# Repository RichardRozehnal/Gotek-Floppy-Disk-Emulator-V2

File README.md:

# Gotek Floppy Disk Emulator V2

Emulátor disketové mechaniky starých počítačů a různých zařízení. Software se do počítače nahrává z obrazu originálního disku (např. ADF pro Amigu), který je uložen na USB flash disku. Tato verze hardwaru využívá firmware [FlashFloppy](https://github.com/keirf/FlashFloppy/wiki), který přidává spoustu nových funkcí a vylepšení oproti standardnímu Goteku. Na uvedém odkazu tvůrce, najdete detailní popisy všech funkcí a nastavení a také nejnovější firmware.

## Seznam součástek

| **Ref**                                                                                                  | **Qnty** | **Value**                   | **Cmp name**                   |
| -------------------------------------------------------------------------------------------------------- | :------: | --------------------------- | ------------------------------ |
| BZ1,                                                                                                     | 1        | 5V Active Buzzer 12mm       | Buzzer                         |
| C1, C2, C4, C7, C8, C9, C10, C12,                                                                        | 8        | 100nF                       | C                              |
| C3, C11,                                                                                                 | 2        | 10uF                        | C                              |
| C5, C6,                                                                                                  | 2        | 22pF                        | C                              |
| C13,                                                                                                     | 1        | 4.7uF/16V                   | CP                             |
| D1,                                                                                                      | 1        | LED Green                   | LED                            |
| D2,                                                                                                      | 1        | 1N4148                      | D                              |
| J1,                                                                                                      | 1        | Power Connector             | Conn\_01x04                    |
| J2,                                                                                                      | 1        | OLED Display 0.91" Module   | OLED\_Display\_0.91"\_Module   |
| J3,                                                                                                      | 1        | USB\_A                      | USB\_A                         |
| J5,                                                                                                      | 1        | Programming Connector       | Conn\_02x05\_Odd\_Even         |
| J6,                                                                                                      | 1        | Floppy Data Connector       | Conn\_02x17\_Odd\_Even         |
| Q1,                                                                                                      | 1        | MMBT2222                    | Q\_NPN\_BEC                    |
| Q2, Q3, Q4, Q5, Q6, Q7,                                                                                  | 6        | BSS123                      | BSS123                         |
| R1,                                                                                                      | 1        | 4K7                         | R                              |
| R2, R3, R7, R8, R9, R10, R11, R12, R13, R14, R15, R16, R17, R18, R19, R20, R21, R22, R23, R24, R25, R26, | 22       | 1K                          | R                              |
| R4, R27                                                                                                  | 2        | 10K                         | R                              |
| R5, R6,                                                                                                  | 2        | 22R                         | R                              |
| SW1,                                                                                                     | 1        | KY040 Rotary Encoder Module | KY040\_Rotary\_Encoder\_Module |
| SW2,                                                                                                     | 1        | DIP Switch                  | DIP\_Switch                    |
| U1,                                                                                                      | 1        | AMS1117-3.3                 | AMS1117-3.3                    |
| U2,                                                                                                      | 1        | STM32F105RBTx               | STM32F105RBTx                  |
| U3,                                                                                                      | 1        | STMPS2141                   | STMPS2141                      |
| U4,                                                                                                      | 1        | 74HCT04                     | 74HCT04                        |
| Y1,                                                                                                      | 1        | 8MHz                        | Crystal                        |

## Oživení

### Programování mikrokontroléru pomocí ST-Link V2

1. stáhněte si a nainstalujte flashovací program STM32-ST-Link Utility na webu [st.com](https://www.st.com/en/development-tools/stsw-link004.html).
2. propojte ST-Link V2 a Gotek V2 vývody SWCLK, SWDIO, GND a +3.3V
3. připojte ST-Link V2 k PC a spusťte flashovací program
4. připojte se na MCU přes menu Target/Connect
5. přes menu File/Open File vyberte soubor FF_Gotek-v3.20.hex (nebo jiný, který chcete nahrát do MCU)
6. spusťte flashování přes menu Target/Program & Verify a Start

### Nastavení DIP přepínače SW2

Pro Amigu, Atari ST a další počítače je nastavení:

| **sig** | **zap/vyp** | **funkce**                              |
| :-----: | :---------: | --------------------------------------- |
| DC1     | OFF         |                                         |
| DC2     | ON          |                                         |
| J5      | OFF         |                                         |
| JC      | OFF         |                                         |
| JB      | ON          | zapnutí/vypnutí emulace zvuku mechaniky |
| S0      | ON          |                                         |
| S1      | OFF         |                                         |

### Příprava USB flash disku a základní operace

1. USB flash disk naformátujte na FAT32 a nahrajte na něj obrazy disků, které budete chtít spouštět, např. ADF pro Amigu
2. připojte Gotek V2 s vloženým USB flash diskem k Amize (místo interního floppy disku), napájecí konektor je dobré před zapojením změřit, abyste do Goteku V2 nepustili 12V místo 5V, kvůli obrácení konektoru!
3. zapněte Amigu, na displeji se zobrazí první z podporovaných souborů, které jste nahráli a rotačním enkodérem mezi nima vybíráte
4. když najedete na soubor a počkáte 2s, tak se automaticky spustí (vloží do floppy mechaniky). Toto je možné v nastavení změnit, aby se automaticky nespouštěl. Potom bude pro vložení do mechaniky nutné stisknout rotační enkodér.
5. pokud chcete změnit orientaci posuvu v souborech (otáčení enkodéru doprava/doleva posouvat soubory nahoru/dolů), je to možné změnit v nastavení.
6. pokud se výběr souborů posune o jednu položku až při dvou nebo čtyřech krocích otočení enkodérem, je možné toto také upravit v nastavení

### Nastavení firmware

1. Gotek V2 funguje s defaultním nastavením i bez konfiguračního souboru
2. pokud však chcete určitou konfiguci změnit, vytvořte na USB flash disku adresář FF a do něj nahrajte konfigurační soubor FF.CFG
3. zrušení automatického spouštění souboru: autoselect-file-secs = 0
4. zrušení automatického vybrání adresáře: autoselect-folder-secs = 0
5. změna orientace posuvu v souborech: rotary = reverse
6. změna kroků enkodéru: rotary = half
7. je možné vybrat i více nastavení najednou, např.: rotary = reverse,half

## Další fotky (vzorky, úprava na BOT straně již není potřeba)

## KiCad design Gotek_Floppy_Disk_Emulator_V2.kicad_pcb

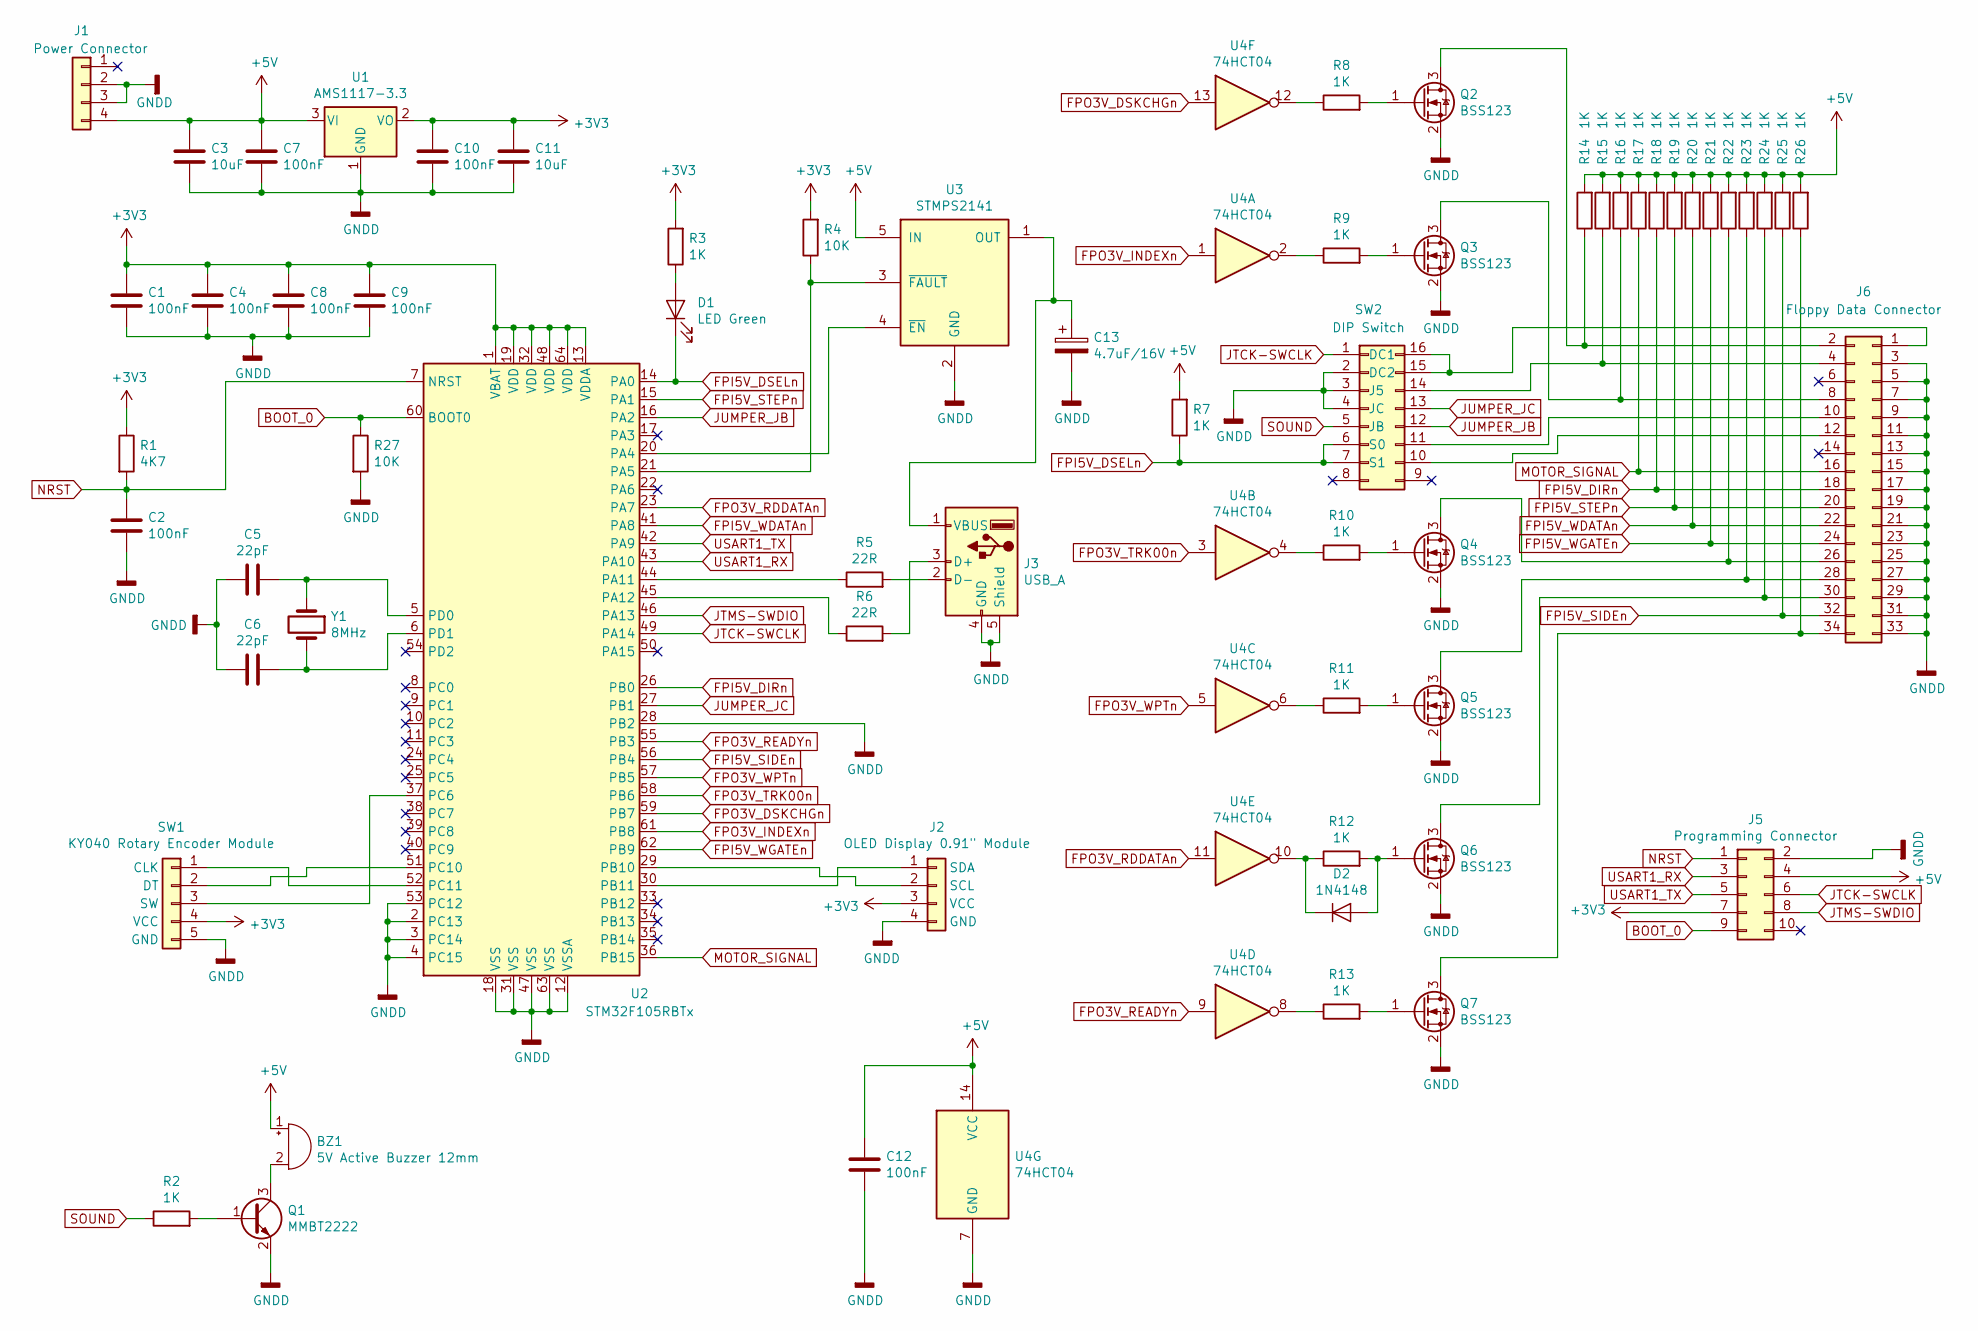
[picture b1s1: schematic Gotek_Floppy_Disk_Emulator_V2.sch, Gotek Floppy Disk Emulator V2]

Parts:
BZ1: 5V Active Buzzer 12mm; Buzzer_12x9.5RM7.6
C1, C2, C4, C7, C8, C9, C10, C12: 100nF; C_1206_3216Metric
C3, C11: 10uF; C_1206_3216Metric
C5, C6: 22pF; C_1206_3216Metric
C13: 4.7uF/16V; CP_EIA-3216-18_Kemet-A
D1: LED Green; LED_D3.0mm
D2: 1N4148; D_MiniMELF
J1: Power Connector; PinHeader_1x04_P2.54mm_Horizontal
J2: OLED Display 0.91\" Module; OLED_Display_0.91_Module
J3: USB_A; USB_A_Stewart_SS-52100-001_Horizontal
J5: Programming Connector; PinHeader_2x05_P2.54mm_Vertical
J6: Floppy Data Connector; PinHeader_2x17_P2.54mm_Horizontal
Q1: MMBT2222; SOT-23
Q2, Q3, Q4, Q5, Q6, Q7: BSS123; SOT-23
R1: 4K7; R_1206_3216Metric
R2, R3, R7, R8, R9, R10, R11, R12, R13, R14, R15, R16, R17, R18, R19, R20, R21, R22, R23, R24, R25, R26: 1K; R_1206_3216Metric
R4, R27: 10K; R_1206_3216Metric
R5, R6: 22R; R_1206_3216Metric
SW1: KY040 Rotary Encoder Module; PinHeader_1x05_P2.54mm_Vertical
SW2: DIP Switch; SW_DIP_SPSTx08_Slide_6.7x21.88mm_W8.61mm_P2.54mm_LowProfile
U1: AMS1117-3.3; SOT-223-3_TabPin2
U2: STM32F105RBTx; LQFP-64_10x10mm_P0.5mm
U3: STMPS2141; SOT-23-5
U4: 74HCT04; SOIC-14_3.9x8.7mm_P1.27mm
Y1: 8MHz; Crystal_HC49-4H_Vertical

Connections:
+3V3: C1.1, C4.1, C8.1, C9.1, C10.1, C11.1, J2.3 (VCC), J5.7, R1.1, R3.2, R4.2, SW1.4 (VCC), U1.2 (VO), U2.1 (VBAT), U2.13 (VDDA), U2.19 (VDD), U2.32 (VDD), U2.48 (VDD), U2.64 (VDD)
+5V: BZ1.1 (-), C3.1, C7.1, C12.1, J1.4, J5.4, R7.2, R14.2, R15.2, R16.2, R17.2, R18.2, R19.2, R20.2, R21.2, R22.2, R23.2, R24.2, R25.2, R26.2, U1.3 (VI), U3.5 (IN), U4.14 (VCC)
BOOT_0: J5.9, R27.1, U2.60 (BOOT0)
FPI5V_DIRn: J6.18, R18.1, U2.26 (PB0)
FPI5V_DSELn: D1.1 (K), R7.1, SW2.6 (S0), SW2.7 (S1), U2.14 (PA0)
FPI5V_SIDEn: J6.32, R25.1, U2.56 (PB4)
FPI5V_STEPn: J6.20, R19.1, U2.15 (PA1)
FPI5V_WDATAn: J6.22, R20.1, U2.41 (PA8)
FPI5V_WGATEn: J6.24, R21.1, U2.62 (PB9)
FPO3V_DSKCHGn: U2.59 (PB7), U4.13
FPO3V_INDEXn: U2.61 (PB8), U4.1
FPO3V_RDDATAn: U2.23 (PA7), U4.11
FPO3V_READYn: U2.55 (PB3), U4.9
FPO3V_TRK00n: U2.58 (PB6), U4.3
FPO3V_WPTn: U2.57 (PB5), U4.5
GNDD: C1.2, C2.2, C3.2, C4.2, C5.2, C6.2, C7.2, C8.2, C9.2, C10.2, C11.2, C12.2, C13.2, J1.2, J1.3, J2.4 (GND), J3.4 (GND), J3.5 (Shield), J5.2, J6.3, J6.5, J6.7, J6.9, J6.11, J6.13, J6.15, J6.17, J6.19, J6.21, J6.23, J6.25, J6.27, J6.29, J6.31, J6.33, Q1.2 (E), Q2.2 (S), Q3.2 (S), Q4.2 (S), Q5.2 (S), Q6.2 (S), Q7.2 (S), R27.2, SW1.5 (GND), SW2.2 (DC2), SW2.3 (J5), SW2.4 (JC), U1.1 (GND), U2.2 (PC13), U2.3 (PC14), U2.4 (PC15), U2.12 (VSSA), U2.18 (VSS), U2.28 (PB2), U2.31 (VSS), U2.47 (VSS), U2.53 (PC12), U2.63 (VSS), U3.2 (GND), U4.7 (GND)
JTCK-SWCLK: J5.6, SW2.1 (DC1), U2.49 (PA14)
JTMS-SWDIO: J5.8, U2.46 (PA13)
JUMPER_JB: SW2.12, U2.16 (PA2)
JUMPER_JC: SW2.13, U2.27 (PB1)
MOTOR_SIGNAL: J6.16, R17.1, U2.36 (PB15)
NRST: C2.1, J5.1, R1.2, U2.7 (NRST)
unnamed: BZ1.2 (+), Q1.3 (C)
unnamed: C5.1, U2.5 (PD0), Y1.1
unnamed: C6.1, U2.6 (PD1), Y1.2
unnamed: C13.1, J3.1 (VBUS), U3.1 (OUT)
unnamed: D1.2 (A), R3.1
unnamed: D2.1 (K), R12.1, U4.10
unnamed: D2.2 (A), Q6.1 (G), R12.2
unnamed: J2.1 (SDA), U2.30 (PB11)
unnamed: J2.2 (SCL), U2.29 (PB10)
unnamed: J3.2 (D-), R5.2
unnamed: J3.3 (D+), R6.2
unnamed: J6.1, SW2.15, SW2.16
unnamed: J6.2, Q2.3 (D), R14.1
unnamed: J6.4, R15.1, SW2.14
unnamed: J6.8, Q3.3 (D), R16.1
unnamed: J6.10, SW2.11
unnamed: J6.12, SW2.10
unnamed: J6.26, Q4.3 (D), R22.1
unnamed: J6.28, Q5.3 (D), R23.1
unnamed: J6.30, Q6.3 (D), R24.1
unnamed: J6.34, Q7.3 (D), R26.1
unnamed: Q1.1 (B), R2.2
unnamed: Q2.1 (G), R8.2
unnamed: Q3.1 (G), R9.2
unnamed: Q4.1 (G), R10.2
unnamed: Q5.1 (G), R11.2
unnamed: Q7.1 (G), R13.2
unnamed: R4.1, U2.21 (PA5), U3.3 (~FAULT)
unnamed: R5.1, U2.44 (PA11)
unnamed: R6.1, U2.45 (PA12)
unnamed: R8.1, U4.12
unnamed: R9.1, U4.2
unnamed: R10.1, U4.4
unnamed: R11.1, U4.6
unnamed: R13.1, U4.8
unnamed: SW1.1 (CLK), U2.52 (PC11)
unnamed: SW1.2 (DT), U2.51 (PC10)
unnamed: SW1.3 (SW), U2.37 (PC6)
unnamed: U2.20 (PA4), U3.4 (~EN)
SOUND: R2.1, SW2.5 (JB)
USART1_RX: J5.3, U2.43 (PA10)
USART1_TX: J5.5, U2.42 (PA9)

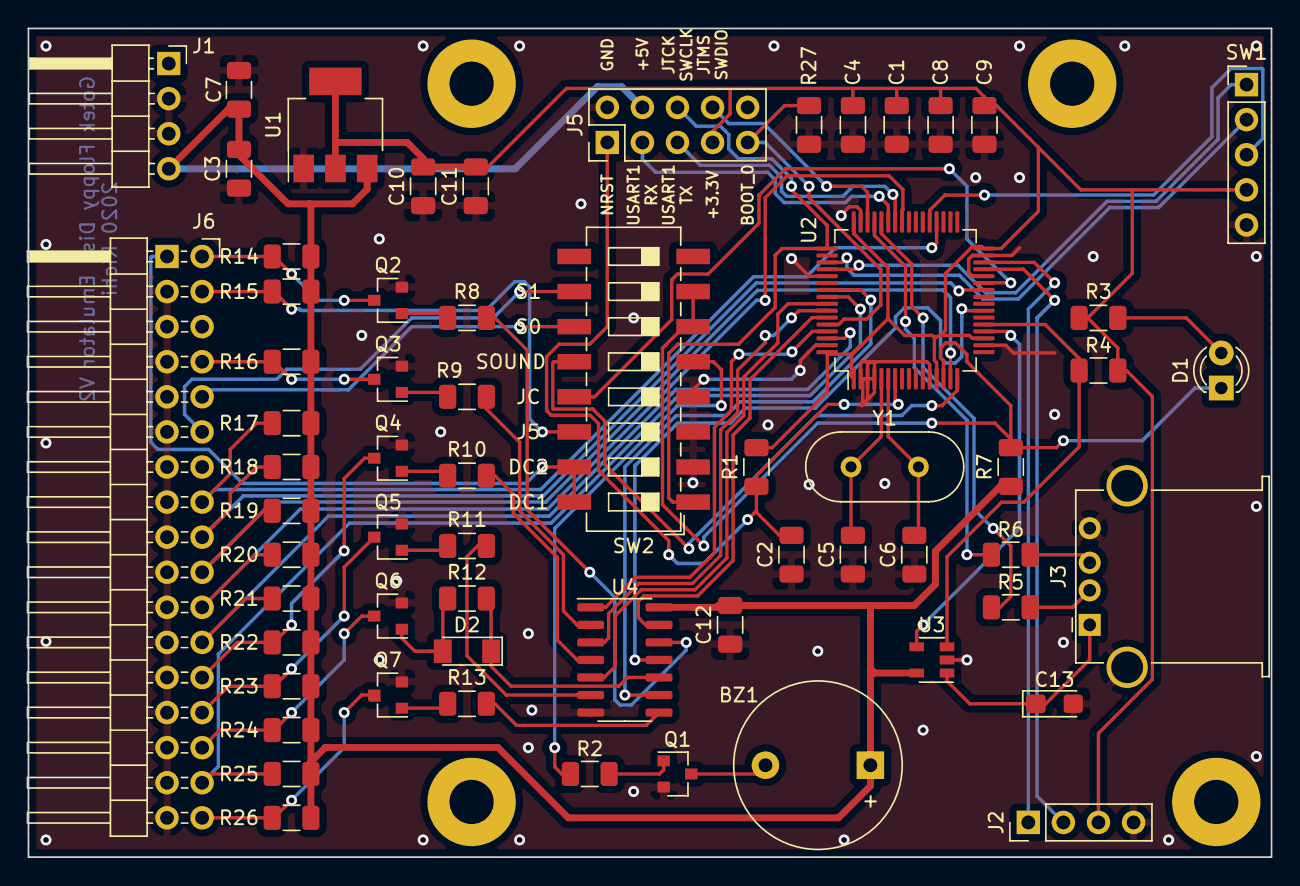
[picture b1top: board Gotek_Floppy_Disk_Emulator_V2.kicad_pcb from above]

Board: 2 copper layers, 90.0 x 60.0 mm, 62 parts (0 on the bottom side), 64 nets.

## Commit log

2020-11-07 Create Firmware
2020-11-07 Create a
2020-12-02 Create LICENSE
